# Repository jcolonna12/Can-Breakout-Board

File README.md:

# Can-Breakout-Board
Can Breakout Board
These are the board and sch files for the can breakout board which were created in Autodesk Eagle.
This board was designed for use in The University of Akron UA Robotics design team's competition robot.

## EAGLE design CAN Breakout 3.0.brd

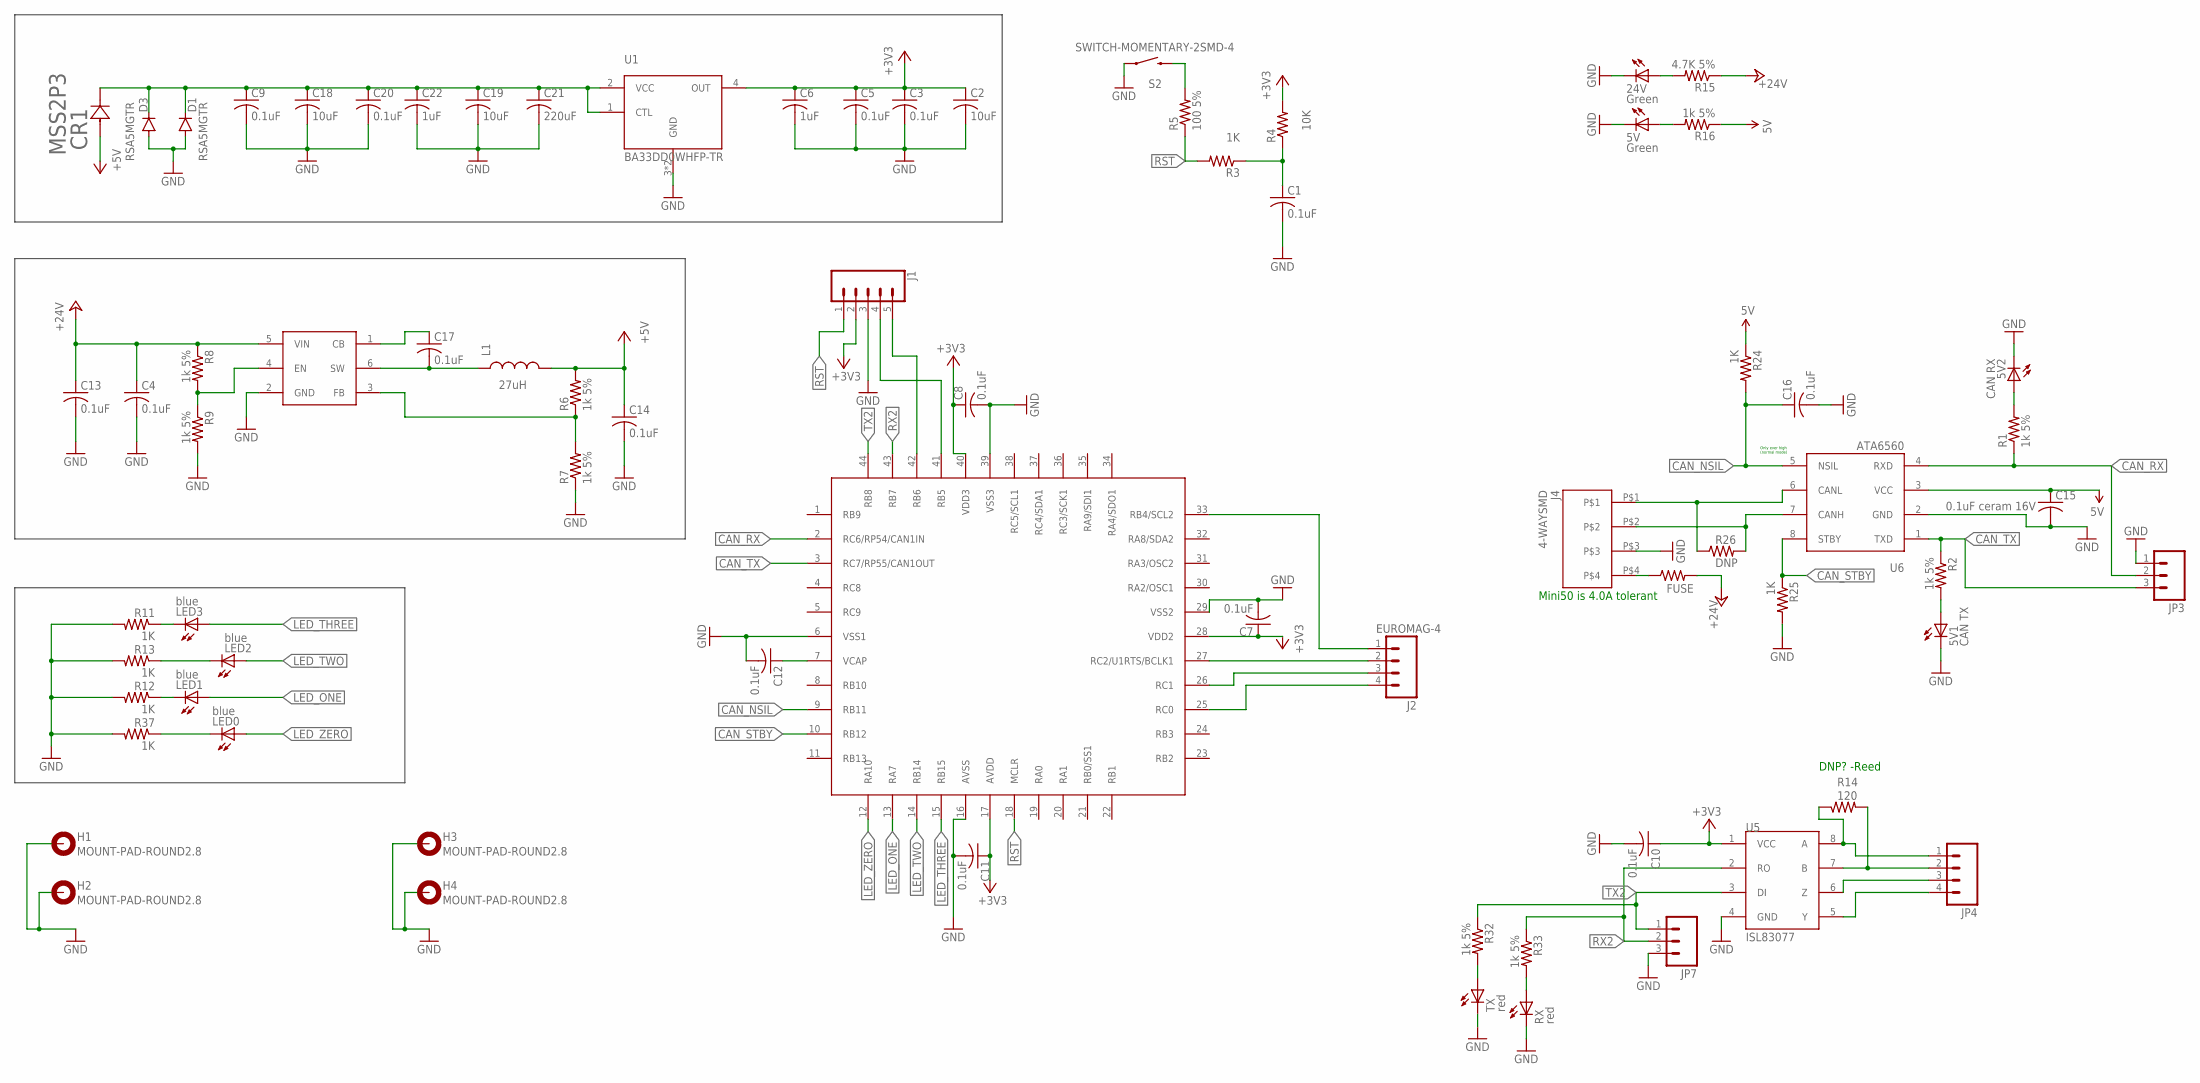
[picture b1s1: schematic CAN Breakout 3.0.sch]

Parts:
5V, 24V: Green; CHIP-LED0805
5V1: CAN TX; CHIP-LED0805
5V2: CAN RX; CHIP-LED0805
C1, C3, C4, C5, C7, C8, C9, C10, C11, C12, C13, C14, C16, C17, C20: 0.1uF; C0805
C2, C18, C19: 10uF; C0805
C6, C22: 1uF; C0805
C15: 0.1uF ceram 16V; C0805
C21: 220uF; C0805
CR1: MSS2P3; DIODE_MSP3V3-L
D1, D3: RSA5MGTR; SOD-123_MINI-SMA
FUSE: RESISTOR1206; 1206
H1, H2, H3, H4: MOUNT-PAD-ROUND2.8; 2,8-PAD
J1: CONN_05; 1X05
J2: EUROMAG-4; M4
J4: 4-WAYSMD; 4-WAY-SMD-90D
JP3, JP7: M03LOCK; 1X03_LOCK
JP4: M04POLAR_LOCK; MOLEX-1X4_LOCK
L1: 27uH; 0805
LED0, LED1, LED2, LED3: blue; CHIPLED_0805
R1, R2, R6, R7, R8, R9, R16, R32, R33: 1k 5%; M0805
R3, R11, R12, R13, R24, R25, R37: 1K; M0805
R4: 10K; M0805
R5: 100 5%; M0805
R14: 120; M0805
R15: 4.7K 5%; M0805
R26: DNP; M0805
RX: red; CHIP-LED0805
S2: SWITCH-MOMENTARY-2SMD-4; TACTILE_SWITCH_TALL
TX: red; CHIP-LED0805
U1: BA33DD0WHFP-TR; HRP5
U2: DSPIC33EP512GP504; TQFP-44
U5: ISL83077; SO08
U6: ATA6560; SOIC8
U7: TPS560430YDBVR; SOT23-6

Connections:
5V: C15.1, R16.1, R24.1, U6.3 (VCC)
+3V3: C2.1, C3.1, C5.1, C6.1, C7.1, C8.1, C10.1, C11.1, J1.2, R4.2, U1.4 (OUT), U2.17 (AVDD), U2.28 (VDD2), U2.40 (VDD3), U5.1 (VCC)
+5V: C14.1, CR1.2, L1.2, R6.2
+24V: C4.1, C13.1, FUSE.2, R8.1, R15.1, U7.5 (VIN)
CAN_NSIL: C16.1, R24.2, U2.9 (RB11), U6.5 (NSIL)
CAN_RX: JP3.2, R1.1, U2.2 (RC6/RP54/CAN1IN), U6.4 (RXD)
CAN_STBY: R25.1, U2.10 (RB12), U6.8 (STBY)
CAN_TX: JP3.3, R2.1, U2.3 (RC7/RP55/CAN1OUT), U6.1 (TXD)
GND: 5V.C, 5V1.C, 5V2.C, 24V.C, C1.2, C2.2, C3.2, C4.2, C5.2, C6.2, C7.2, C8.2, C9.2, C10.2, C11.2, C12.2, C13.2, C14.2, C15.2, C16.2, C18.2, C19.2, C20.2, C21.2, C22.2, D1.A, D3.A, H1.B2,8, H2.B2,8, H3.B2,8, H4.B2,8, J1.3, J4.P$3, JP3.1, JP7.3, R7.1, R9.2, R11.2, R12.2, R13.2, R25.2, R37.2, RX.C, S2.A2 (1), TX.C, U1.3 (GND), U1.G (GND), U2.6 (VSS1), U2.16 (AVSS), U2.29 (VSS2), U2.39 (VSS3), U5.4 (GND), U6.2 (GND), U7.2 (GND)
LED_ONE: LED1.A, U2.13 (RA7)
LED_THREE: LED3.A, U2.15 (RB15)
LED_TWO: LED2.A, U2.14 (RB14)
LED_ZERO: LED0.A, U2.12 (RA10)
unnamed: 24V.A, R15.2
unnamed: J1.5, U2.42 (RB6)
unnamed: J2.2, U2.27 (RC2/U1RTS/BCLK1)
unnamed: J1.4, U2.41 (RB5)
unnamed: J2.3, U2.26 (RC1)
unnamed: C9.1, C18.1, C19.1, C20.1, C21.1, C22.1, CR1.1, D1.C, D3.C, U1.1 (CTL), U1.2 (VCC)
unnamed: J2.1, U2.33 (RB4/SCL2)
unnamed: 5V2.A, R1.2
unnamed: J2.4, U2.25 (RC0)
unnamed: 5V.A, R16.2
unnamed: 5V1.A, R2.2
unnamed: LED0.C, R37.1
unnamed: LED2.C, R13.1
unnamed: J4.P$1, R26.1, U6.6 (CANL)
unnamed: LED1.C, R12.1
unnamed: R5.2, S2.B2 (2)
unnamed: C1.1, R3.1, R4.1
unnamed: FUSE.1, J4.P$4
unnamed: JP4.2, R14.2, U5.7 (B)
unnamed: JP4.1, R14.1, U5.8 (A)
unnamed: JP4.3, U5.6 (Z)
unnamed: JP4.4, U5.5 (Y)
unnamed: LED3.C, R11.1
unnamed: C17.2, L1.1, U7.6 (SW)
unnamed: R8.2, R9.1, U7.4 (EN)
unnamed: C17.1, U7.1 (CB)
unnamed: R6.1, R7.2, U7.3 (FB)
unnamed: R32.2, TX.A
unnamed: J4.P$2, R26.2, U6.7 (CANH)
unnamed: C12.1, U2.7 (VCAP)
unnamed: R33.2, RX.A
RST: J1.1, R3.2, R5.1, U2.18 (MCLR)
RX2: JP7.2, R33.1, U2.43 (RB7), U5.2 (RO)
TX2: JP7.1, R32.1, U2.44 (RB8), U5.3 (DI)

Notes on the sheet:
Only ever high (normal mode)
DNP? -Reed
Mini50 is 4.0A tolerant

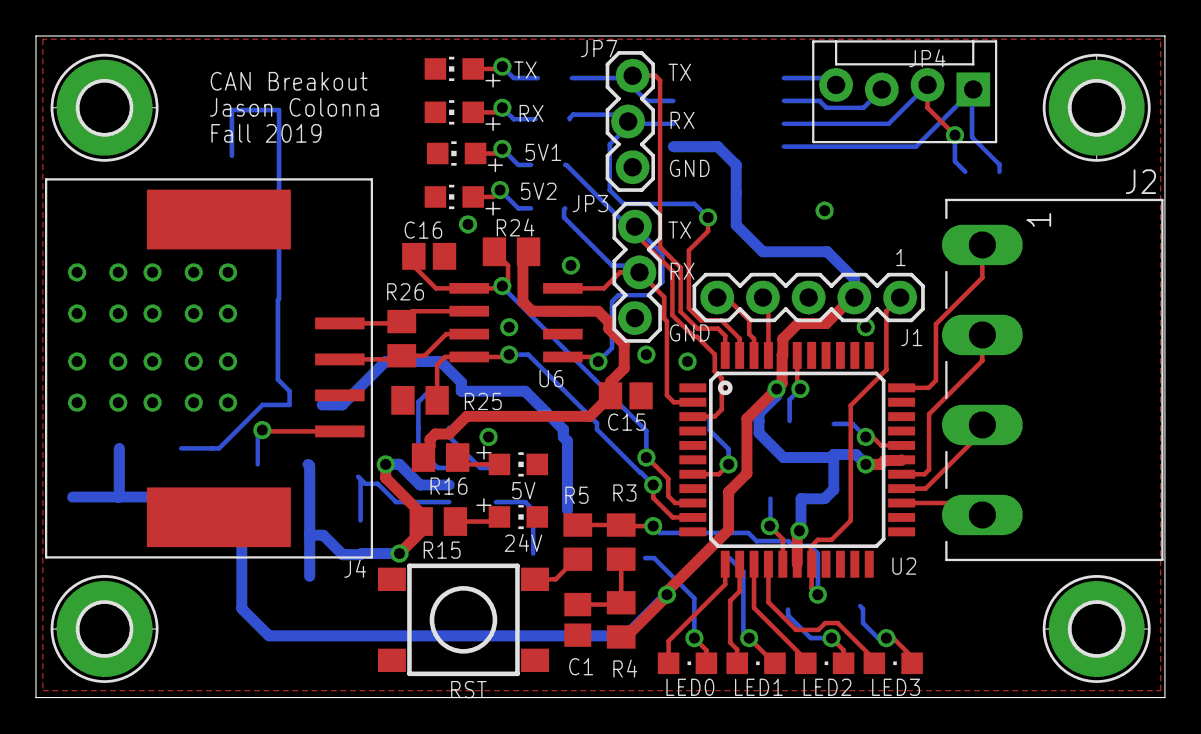
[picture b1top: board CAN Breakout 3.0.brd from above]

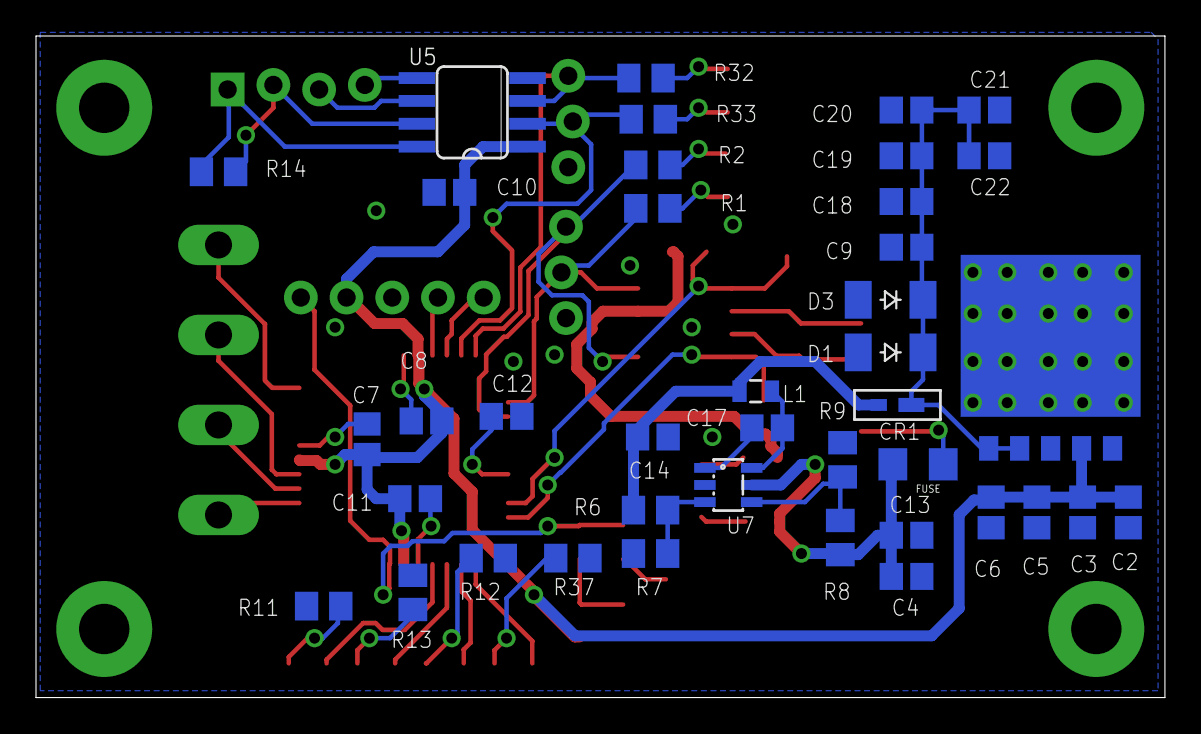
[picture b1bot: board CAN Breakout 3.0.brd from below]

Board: 2 copper layers, 62.7 x 36.8 mm, 74 parts (40 on the bottom side), 47 nets.

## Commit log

2019-12-25 PCB Gerber Files

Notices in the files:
parts and their libraries:
SparkFun-Connectors: Licensing: Creative Commons ShareAlike 4.0 International - https://creativecommons.org/licenses/by-sa/4.0
SparkFun: Licensing: CC v3.0 Share-Alike You are welcome to use this library for commercial purposes.
